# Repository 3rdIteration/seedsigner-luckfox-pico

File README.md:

# seedsigner-luckfox-pico
Port of the SeedSigner code to support the LuckFox Pico Linux board family. Since this device is still an embedded Linux device, like the Raspberry Pi, the changes are fairly minimal in order to access the buttons and the camera. This repo mostly pertains to the Buildroot OS build instructions, the KiCAD schematic and PCB design files, and 3D models of cases for the assembled device.

SeedSigner code fork: https://github.com/3rdIteration/seedsigner/tree/dev

## Hardware Photos
_Most Recent Iteration: LuckFox Pico Mini B with no onboard SPI flash_

_Previous Iteration: LuckFox Pico Pro Max (More Flash, SPI Flash)_

## Demo Videos

### First Look: SeedSigner running on LuckFox Pico Linux devboard

## Materials Needed
Check out the shopping list for a parts list of various LuckFox-based hardware configurations: [here](docs/shopping_list.md)

These example builds can build a device for around $60.

## OS Image Build with Buildroot

### Build with GitHub Actions (Recommended for Most Users)
The easiest way to build the SeedSigner OS image is using GitHub Actions. This method builds directly on GitHub's infrastructure without requiring Docker:

1. Fork this repository to your GitHub account
2. Navigate to the "Actions" tab in your fork
3. Select the "Build SeedSigner OS" workflow
4. The workflow runs automatically on pushes to `main`, `develop`, or `master` branches
5. Builds are created for both LuckFox Pico Mini (RV1103) and Pro Max (RV1106) hardware
6. Wait for the build to complete (typically 60-120 minutes)
7. Download the artifacts from the workflow run

The GitHub Actions workflow:
- Installs all required dependencies on Ubuntu 22.04
- Clones the LuckFox Pico SDK (customized fork), SeedSigner code, and SeedSigner OS packages
- Configures buildroot with SeedSigner-specific packages
- Builds the complete OS image
- Creates flashable SD card images and NAND flash bundles for SD_CARD and SPI_NAND boot media
- Provides detailed build summaries and flashing instructions

### Build Locally with Docker (Simple Method)
For users who want to build locally, a simple build script is available:

```bash
cd buildroot/
./build.sh build --microsd
```

Build artifacts will be automatically available in `buildroot/build-output/`. The script handles Docker image building, repository caching, and artifact export automatically.

**Additional options:**
- `--nand` - Build NAND flash bundles
- `--model mini` or `--model max` - Build specific hardware only
- `--jobs N` - Use N parallel jobs
- See `./build.sh --help` for all options

### Build Locally Without Docker (Advanced Users)
For development or if you prefer not to use Docker, an automated local build script is available (Ubuntu 22.04):

```bash
cd buildroot/
./build-local.sh --check-deps  # Install dependencies (first time)
./build-local.sh               # Build for Mini with SD card
```

**Additional options:**
- `--hardware mini|max` - Choose hardware type
- `--boot sd|nand` - Choose boot medium
- See `./build-local.sh --help` for all options

For more details and manual step-by-step instructions, see [OS-build-instructions.md](docs/OS-build-instructions.md).
For Luckfox runtime startup order, camera service sequencing, and Mini memory/timing behavior, see [LUCKFOX_STARTUP_WORKFLOW.md](docs/LUCKFOX_STARTUP_WORKFLOW.md).

## Dev Machine Setup

### Install ADB
Developing for the LuckFox Pico device is quite convenient since the devices never connect to the internet and you can access the device shell using `adb`. You can push files back and forth to your dev machine, and you can access the device as a shell easily.
```
# mac
brew install homebrew/cask/android-platform-tools

# linux
sudo apt install android-tools-adb
```

### ADB Connection and Device Management

1. Connect to the device:
```
# List connected devices
adb devices

# Connect to device shell
adb shell
```

2. File Operations:
```
# Push files to device
adb push local_file.txt /remote/path/

# Sync the code repo for local development
adb push /repos/seedsigner/src /seedsigner

# Pull files from device
adb pull /seedsigner/config.json .

# List files on device
adb shell ls /path/to/directory
```

## Hardware Identification
Notice the left device has an empty PCB footprint pattern on it. This is where the optional SPI flash is soldered on. For the SeedSigner project we don't want permanent storage, so avoid devices with soldered SPI flash.

```
LEFT:  LuckFox Pico Mini A -> No Flash
RIGHT: LuckFox Pico Mini B -> Soldered Flash
```

## Flashing the Device

### Flash MicroSD Card
```
sudo dd bs=4M status=progress if=seedsigner-luckfox-pico-YYYYmmdd_hhmmss.img of=/dev/diskX
```
Replace `/dev/diskX` with your actual SD card device path.

## LuckFox Pico OS Modifications
We have forked the [LuckFox Pico SDK](https://github.com/3rdIteration/luckfox-pico) in order to enable various hardware features like pull-up resistors, adjust video RAM, and other things.

### Camera Memory
The LuckFox devotes some of its memory for camera-related algorithms, but we don't use this feature. Particularly on the LuckFox Pico Mini device, which only has 64MB of RAM, it is beneficial for us to reclaim a bit of this memory.

**Note:** The GitHub Actions workflow automatically sets the CMA (Contiguous Memory Allocator) size to 1M for Mini builds, freeing up approximately 20MB of RAM. This is configured by modifying `RK_BOOTARGS_CMA_SIZE` in the board configuration file.

Memory usage WITHOUT modification:
```bash
[root@luckfox ]# free -h
              total        used        free      shared  buff/cache   available
Mem:          33.0M       24.3M        1.4M      476.0K        7.3M        5.4M
Swap:             0           0           0
```

Memory usage WITH modification:
```bash
[root@luckfox ]# free -h
              total        used        free      shared  buff/cache   available
Mem:          53.0M       23.6M        1.9M      472.0K       27.5M       25.3M
Swap:             0           0           0
```

### Pull-up Resistors
Our current dev board has external pull-up resistors, since we didn't know how to enable these at the time, and it is always smart to plan ahead when designing PCBs. NOTE: Even with this commit and this change, the internal pull-ups don't seem to work.

### SPI Buffer Size
While it is possible to send SPI data in chunks, you can increase the SPI buffer size to slightly increase throughput, which is useful for larger displays.

### PWM Output
In order to control the LCD screen backlight and support true dimming of the display (instead of just changing the background color of the QR code, for example), we had to enable a PWM on a specific output pin.

## Support the Developer
If you find this project helpful and would like to support its development, you can buy me a coffee! Your support helps keep this project going and funds future improvements. Help decentralize Bitcoin hardware!

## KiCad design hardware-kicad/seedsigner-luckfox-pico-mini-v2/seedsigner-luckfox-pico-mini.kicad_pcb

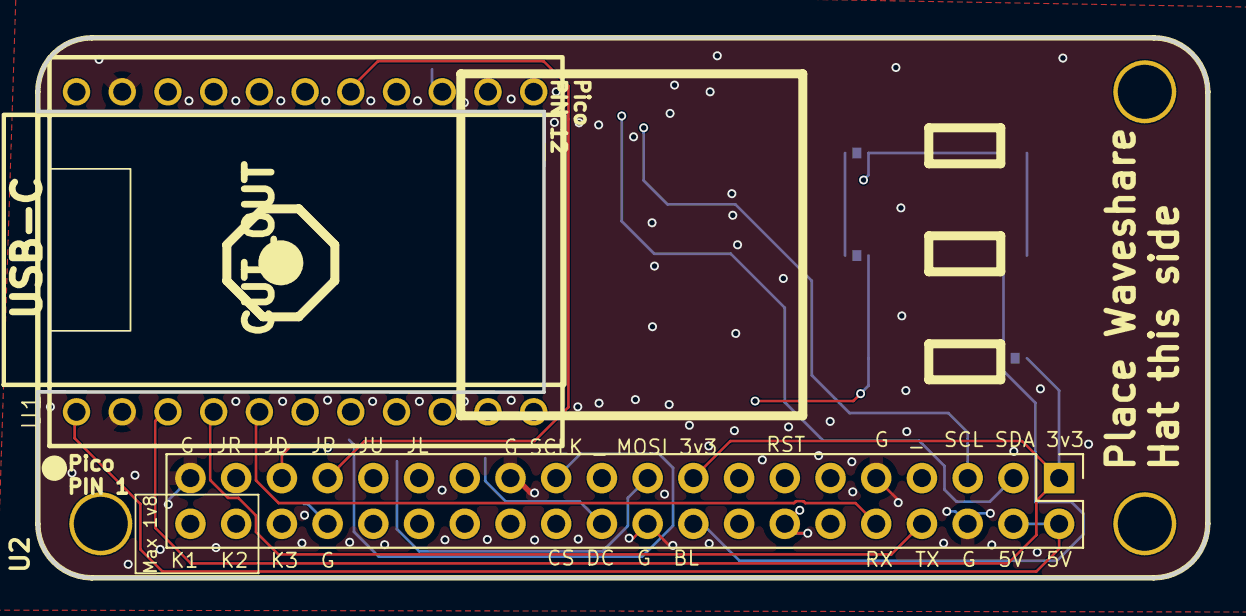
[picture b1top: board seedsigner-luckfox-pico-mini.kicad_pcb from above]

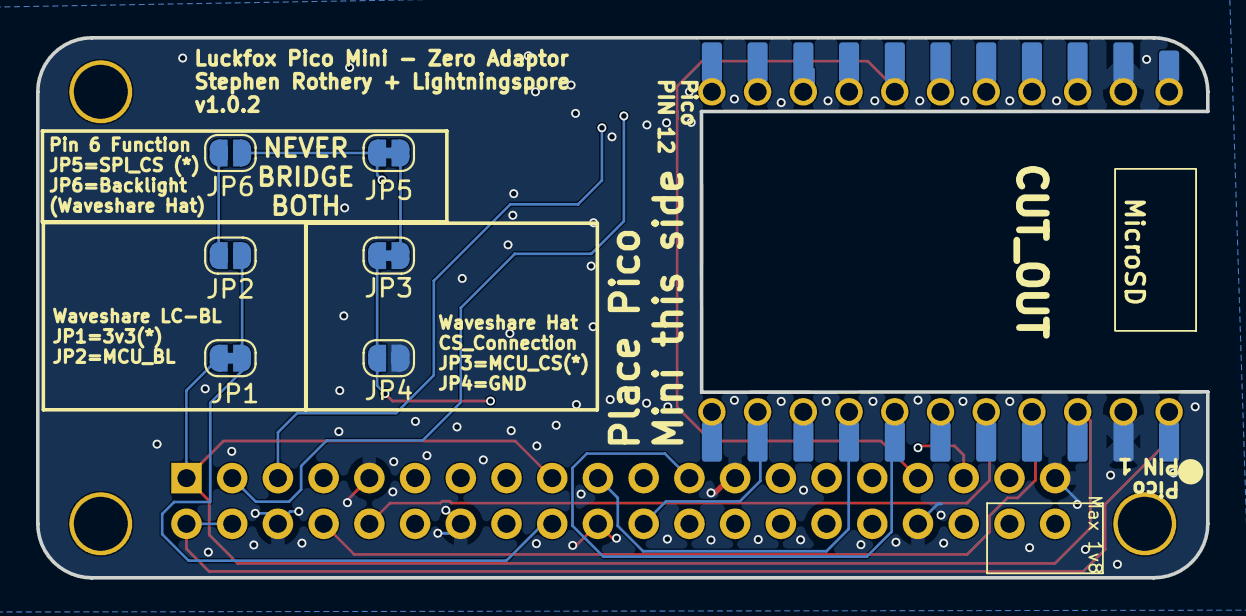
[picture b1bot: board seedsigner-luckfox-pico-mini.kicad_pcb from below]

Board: 4 copper layers, 65.0 x 30.0 mm, 8 parts (6 on the bottom side), 24 nets.

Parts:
JP1, JP3, JP5: Jumper_2_Small_Bridged; SolderJumper-2_P1.3mm_Bridged_RoundedPad1.0x1.5mm
JP2, JP4, JP6: Jumper_2_Small_Open; SolderJumper-2_P1.3mm_Open_RoundedPad1.0x1.5mm
U1: LuckFox_Pico_MINI; LUCKFOX_PICO_MINI
U2: WAVESHARELCD_PLUS_UART_PLUS_I2C; WAVESHARE_LCD_BUTTON

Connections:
+3.3V: JP1.1 (A), U1.3 (3V3(OUT)), U2.1 (3V3), U2.17 (3V3)
+5V: U1.1 (VBUS), U2.2 (5V0), U2.4 (5V0)
/DC: U1.10 (GPIO1_C4_d), U2.22 (DC)
/I2C-SCL: U1.15 (GPIO1_D3_d), U2.5 (I2C-SCL)
/I2C-SDA: U1.14 (GPIO1_D2_d), U2.3 (I2C-SDA)
/JOYSTICK_DOWN: U1.17 (GPIO1_C7_d), U2.35 (JS_DOWN)
/JOYSTICK_LEFT: U1.12 (GPIO1_D0_d), U2.29 (JS_LEFT)
/JOYSTICK_PRESS: U1.16 (GPIO1_C6_d), U2.33 (JS_PRESS)
/JOYSTICK_RIGHT: U1.18 (GPIO0_A4_d), U2.37 (JS_RIGHT)
/JOYSTICK_UP: U1.13 (GPIO1_D1_d), U2.31 (JS_UP)
/KEY1: U1.19 (GPIO4_C0_z), U2.40 (KEY1)
/KEY2: U1.20 (GPIO4_C1_z), U2.38 (KEY2)
/KEY3: U1.11 (GPIO1_C5_d), U2.36 (KEY3)
/MCU_BACKLIGHT: JP2.1 (A), JP6.1 (A)
/MCU_SPI_CS: JP3.1 (A), JP5.1 (A)
/RPI_BACKLIGHT: JP1.2 (B), JP2.2 (B), U2.18 (BACKLIGHT)
/RPI_SPI_CS: JP3.2 (B), JP4.2 (B), U2.24 (~SPI_CS0)
/RST: U1.9 (SPI0_MISO_M0/GPIO1_C3_d), U2.13 (RESET)
/SPI_MOSI: U1.8 (SPI0_MOSI_M0/GPIO1_C2_d), U2.19 (SPI_MOSI)
/SPI_SCLK: U1.7 (SPI0_CLK_M0/IO1_C1_d), U2.23 (SPI_SCLK)
/UART_RXD: U1.5 (GPIO1_B3_u), U2.10 (UART-RXDO)
/UART_TXD: U1.4 (GPIO1_B2_d), U2.8 (UART-TXDO)
GND: JP4.1 (A), U1.2 (GND), U1.21 (GND), U2.6 (GND), U2.9 (GND), U2.14 (GND), U2.20 (GND), U2.25 (GND), U2.30 (GND), U2.34 (GND), U2.39 (GND)
unnamed: JP5.2 (B), JP6.2 (B), U1.6 (SPI0_CS0_M0/IO1_C0_d)

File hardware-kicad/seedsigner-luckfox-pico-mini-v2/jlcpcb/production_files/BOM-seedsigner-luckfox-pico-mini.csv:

Comment,Designator,Footprint,LCSC,Quantity
LuckFox_Pico_MINI,U1,LUCKFOX_PICO_MINI,,1
WAVESHARELCD_PLUS_UART_PLUS_I2C,U2,WAVESHARE_LCD_BUTTON,,1
Jumper_2_Small_Open,JP2,SolderJumper-2_P1.3mm_Open_RoundedPad1.0x1.5mm,,1
Jumper_2_Small_Open,JP4,SolderJumper-2_P1.3mm_Open_RoundedPad1.0x1.5mm,,1
Jumper_2_Small_Open,JP6,SolderJumper-2_P1.3mm_Open_RoundedPad1.0x1.5mm,,1
Jumper_2_Small_Bridged,JP3,SolderJumper-2_P1.3mm_Bridged_RoundedPad1.0x1.5mm,,1
Jumper_2_Small_Bridged,JP1,SolderJumper-2_P1.3mm_Bridged_RoundedPad1.0x1.5mm,,1
Jumper_2_Small_Bridged,JP5,SolderJumper-2_P1.3mm_Bridged_RoundedPad1.0x1.5mm,,1

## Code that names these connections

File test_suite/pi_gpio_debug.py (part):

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    KEY_RIGHT = GPIO0_A0  gpiochip0/0
    KEY_DOWN  = GPIO0_A1  gpiochip0/1
    KEY_PRESS = GPIO1_C4  gpiochip1/20
    KEY3      = GPIO1_C7  gpiochip1/23
    KEY_UP    = GPIO3_D1  gpiochip3/25
    KEY_LEFT  = GPIO3_D2  gpiochip3/26
    KEY2      = GPIO3_D3  gpiochip3/27
    KEY1      = GPIO4_C1  gpiochip4/17

Register addresses from docs/RV1106_GPIO_User_Manual.txt
(extracted from Rockchip_RV1106_User_Manual_GPIO.pdf).
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    ("KEY_UP",    3, 25,   0xFF558058,  6, 4,  0xFF5581AC,  1,  0xFF5581EC,  3, 2, 'std',   0xFF55000C,  9,  0xFF550074,  9),
    ("KEY_LEFT",  3, 26,   0xFF558058, 10, 8,  0xFF5581AC,  2,  0xFF5581EC,  5, 4, 'std',   0xFF55000C, 10,  0xFF550074, 10),
    ("KEY2",      3, 27,   0xFF558058, 14,12,  0xFF5581AC,  3,  0xFF5581EC,  7, 6, 'std',   0xFF55000C, 11,  0xFF550074, 11),
    ("KEY1",      4, 17,   0xFF568010,  6, 4,  0xFF5680C0,  3,  0xFF5680C0, 14,13, 'gpio4hd', 0xFF56000C, 1, 0xFF560074,  1),
]


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        (0xFF388030, 0x00030003, 'GPIO0 input buffer enable'),
        (0xFF388038, 0x000F0005, 'GPIO0 pull-up'),
        (0xFF380008, 0x00030000, 'GPIO0 direction → input'),
        # GPIO1: KEY_PRESS (C4) + KEY3 (C7)
        (0xFF538014, 0x70070000, 'GPIO1 IOMUX → GPIO'),
        (0xFF538188, 0x00900090, 'GPIO1 input buffer enable'),
        (0xFF5381C8, 0xC3004100, 'GPIO1 pull-up'),
        (0xFF53000C, 0x00900000, 'GPIO1 direction → input'),
        # GPIO3: KEY_UP (D1) + KEY_LEFT (D2) + KEY2 (D3)
        (0xFF558058, 0x77700000, 'GPIO3 IOMUX → GPIO'),
        (0xFF5581AC, 0x000E000E, 'GPIO3 input buffer enable'),
        (0xFF5581EC, 0x00FC0054, 'GPIO3 pull-up'),
        (0xFF55000C, 0x0E000000, 'GPIO3 direction → input'),
        # GPIO4: KEY1 (C1) — high-drive pad, pull encoding: 3=pullup
        (0xFF568010, 0x00700000, 'GPIO4 IOMUX → GPIO'),
        (0xFF5680C0, 0x60086008, 'GPIO4 pull-up + input buffer enable'),
        (0xFF56000C, 0x00020000, 'GPIO4 direction → input'),
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    print('    gpioget -c gpiochip0 0   # KEY_RIGHT')
    print('    gpioget -c gpiochip0 1   # KEY_DOWN')
    print('    gpioget -c gpiochip1 20  # KEY_PRESS')
    print('    gpioget -c gpiochip1 23  # KEY3')
    print('    gpioget -c gpiochip3 25  # KEY_UP')
    print('    gpioget -c gpiochip3 26  # KEY_LEFT')
    print('    gpioget -c gpiochip3 27  # KEY2')
    print('    gpioget -c gpiochip4 17  # KEY1')
    print()
    print('  Force IOMUX → GPIO for all button pins via kernel pinctrl:')
    print('    gpioget -c gpiochip0 0 1')
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
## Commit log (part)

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2026-02-11 Fix cryptography cargo target injection order for armv7
2026-02-11 Use GCC 11 buildroot toolchain for libcamera compatibility
2026-02-12 Add workflow_dispatch toggles for build and hardware targets
2026-02-12 Align GitHub build workflow with local build.sh invocation
2026-02-12 Make CI builds deterministic with optional upstream ref pinning
2026-02-13 CI: checkout workflow repo with recursive submodules
2026-02-13 Use recursive checkout for CI Docker and local jobs
2026-02-13 Pin SDK to external Buildroot defconfig
2026-02-13 Add CI rootfs UBI sanity checks and debug logging
2026-02-13 Add local build diagnostics and rootfs sanity checks
2026-02-13 Build: run rootfs UBI sanity checks only for NAND outputs
2026-02-13 CI: split mini/max x sd/nand builds and collect NAND debug artifacts
2026-02-13 Fix workflow concurrency expression to avoid matrix context error
2026-02-13 Fix matrix medium filter expression in workflow
2026-02-13 Polish NAND sanity command formatting
2026-02-13 Force required Buildroot packages and rootfs overlay
2026-02-13 Fix BR2_DEFCONFIG rewrite quoting after script refactor
2026-02-13 Fix SIGPIPE 141 in Buildroot dir discovery
2026-02-13 Require dynamic eudev device management in Buildroot config checks
2026-02-13 Fix export_variant_images to copy files directly to OUTPUT_DIR
    The export_variant_images function was creating a subdirectory
    ${board_profile}-${boot_medium}-images inside OUTPUT_DIR, causing
    GitHub Actions to fail finding rootfs.img. Changed to copy files
    directly to OUTPUT_DIR to match workflow expectations.
2026-02-13 Address code review feedback: combine sed calls and simplify logic
    - Combined multiple sed invocations into single command for better performance
    - Simplified eudev configuration logic to unconditionally ensure BR2_PACKAGE_EUDEV is set
    - Removed confusing conditional that was always setting the same value
2026-02-13 Fix buildroot config fragment to disable conflicting device creation methods
2026-02-14 Add explicit permissions to workflow jobs for security
    - Add permissions block to setup job (contents: read)
    - Add permissions block to build job (contents: read, actions: write)
    - Fixes CodeQL security alerts about missing workflow permissions
2026-02-14 Fix shell script issues in workflow for better handling of filenames with spaces
2026-02-14 Fix artifact duplication - filter by model in uploads
    - Modified "Package NAND bundle zips" to only process current model's bundles
    - Updated artifact upload paths to be model-specific using matrix.model
    - Updated "List build artifacts" to show only current model's files
    - Updated "Build summary" to filter artifacts by model
    - This ensures each job only uploads artifacts for its specific model/medium combination
2026-02-14 Remove tar.gz NAND bundles - only keep zip format
    - Removed tar.gz creation from os-build.sh create_nand_image_artifacts
    - Removed export_official_nand_image_dir function (only created tar.gz)
    - Removed tar.gz from workflow artifact upload paths
    - Removed tar.gz listing and summary sections from workflow
    - Updated documentation to reflect single zip format
    - NAND bundles now only created as .zip for cross-platform compatibility
2026-02-14 Improve code maintainability: add SYSTEM_INDEX variable and share board config path
2026-02-14 Add repository URL inputs to GitHub Actions workflow for flexibility
2026-02-14 Fix pyzbar library path by symlinking zbar.so from site-packages to /usr/lib
2026-02-14 Fix documentation inconsistencies based on code review
2026-02-14 Fix dependency detection in build-local.sh using dpkg-query
2026-02-14 Add comprehensive documentation for libcamera build fix
2026-02-15 Update SDK to 3rdIteration/luckfox-pico with GCC 13 support
    This fixes the build failure caused by libcamera requiring GCC 9.0+
    The previous SDK (lightningspore/luckfox-pico) used an older GCC version
    Changes:
    - Update GitHub Actions workflow to use 3rdIteration/luckfox-pico@copilot/enable-glibc-highest-version
    - Update all build scripts to use the new SDK repository and branch
    - Update documentation to reflect the new SDK location
2026-02-15 Switch local and CI builds to glibc LuckFox SDK
2026-02-15 Add SDK compiler alias fallback for buildroot_create
2026-02-15 Fix stub toolchain interfering with actual compilation
    The stub toolchain was being added to GITHUB_PATH, which persists
    across all workflow steps. This caused the stub to be used during
    actual compilation (u-boot build), which failed as designed.
    Changed to only export PATH within the "Prepare buildroot source tree"
    step, so the stub is only available for the Makefile.param check.
    Subsequent build steps (u-boot, kernel, rootfs) will use buildroot's
2026-02-15 Update documentation with build.sh validation fix
2026-02-15 Build buildroot with 'make buildroot' to create toolchain and runtime libs
    The previous approach of using './build.sh rootfs' failed because it
    expected runtime libraries at /tmp/runtime_lib, which are only created
    during the full buildroot build process.
    Changed to use 'make buildroot -C sysdrv' which:
    1. Builds buildroot's internal GCC 13 toolchain
    2. Creates runtime libraries in /tmp/runtime_lib
2026-02-15 Fix build failure by copying rootfs-overlay to expected location
2026-02-15 Upgrade to buildroot 2024.11.1 with Python 3.12
2026-02-15 Fix all placeholder hashes with correct SHA256 checksums
    - nfc-bindings: updated from placeholder to d5a562ee...
    - openct: updated from placeholder to f1ba0147...
    - python-pyscard: updated from placeholder (v2.1.1) to correct hash for v2.3.1
    All hashes verified by downloading actual release tarballs from GitHub.
2026-02-15 Fix build: remove python-cryptography and dependencies from buildroot
    Remove BR2_PACKAGE_PYTHON_CRYPTOGRAPHY, BR2_PACKAGE_PYTHON_PYASN1, and
    BR2_PACKAGE_PYTHON_PYOPENSSL from buildroot defconfig and python-pgpy
    dependencies.
    These packages will be installed by SeedSigner's pip installation instead.
    python-cryptography in buildroot 2024.11.x has Rust components that fail
    to cross-compile for ARM. seedsigner-os uses buildroot 2023.02.x which has
2026-02-16 Fix opencv-mobile package: correct version tag and Python paths
    - Use version 35 (tag v35) instead of 4.13.0
    - Update hash to match v35 tarball (4411be32...)
    - Fix Python CMake variables: PYTHON3_INCLUDE_PATH and PYTHON3_PACKAGES_PATH
    - Remove PYTHON3_NUMPY_INCLUDE_DIRS (automatically detected by OpenCV)
    - Fix HOST_DIR path from /bin to /usr/bin
    These fixes address code review feedback and ensure proper build configuration.
2026-02-16 Disable opencv-mobile due to numpy GCC requirement, revert to custom NV12 converter
    NumPy requires GCC >= 8.4 but LuckFox toolchain has older GCC version.
    opencv-mobile Python bindings require numpy, which cannot be built.
    Changes:
    - Disabled BR2_PACKAGE_OPENCV_MOBILE in defconfig
    - Disabled BR2_PACKAGE_OPENCV_MOBILE_PYTHON in defconfig
    - Reverted default branch to claude/add-luckfox-pico-support-AO5ZX
2026-02-16 Use buildroot's bundled numpy and new LuckFox SDK branch with higher uclibc
    Removed custom python-numpy package and switched to using buildroot's bundled
    numpy. The new LuckFox SDK branch (copilot/build-python-with-uclib-nh) has a
    higher version of uclibc that should support the GCC requirements for numpy.
    Changes:
    - Removed buildroot/external-packages/python-numpy/ directory entirely
    - Removed python-numpy from Computer Vision menu in workflow
2026-02-16 Fix legacy configuration error: Create minimal clean defconfig
    The build was failing with "legacy configuration" error because the defconfig
    had 517 lines of auto-generated computed values (BR2_TOOLCHAIN_HEADERS_AT_LEAST_*,
    BR2_PACKAGE_*_ARCH_SUPPORTS, etc.) that shouldn't be in a defconfig file.
    Created a minimal defconfig (~140 lines) with only the explicitly user-selected
    options:
    - Architecture: ARM Cortex-A7, hard float, VFPv4
2026-02-16 Fix legacy configuration: Remove BR2_PACKAGE_OVERRIDE_FILE and empty post-script options
    Removed legacy/problematic configuration options that were causing the
    "legacy configuration" error:
    - BR2_PACKAGE_OVERRIDE_FILE (not standard, using invalid path)
    - BR2_ROOTFS_POST_IMAGE_SCRIPT="" (empty value, not needed)
    - BR2_ROOTFS_POST_SCRIPT_ARGS="" (empty value, not needed)
    These options were likely triggering buildroot's legacy configuration check.
2026-02-17 Enable rng-tools for hardware random number generation
2026-02-17 Enable libgpiod2 library and tools for GPIO control
2026-02-17 Complete SPI-NAND investigation: partition layout and space analysis
2026-02-17 Add implementation summary for automated patch system
2026-02-17 Add documentation for GitHub Actions workflow triggers
2026-02-17 Add python-pyscard and python-pysatochip smartcard support packages
2026-02-17 Fix python-pyscard build failure by adding pcsc-lite dependency
2026-02-17 Fix userdata removal from partition filesystem configuration
2026-02-19 Add comprehensive planning document for camera service management
2026-02-19 Expand Pro Max rootfs to 227MB for 256MB flash
2026-02-19 Fix rkipc patch timing and stabilize camera init startup
2026-02-20 Increase delayed rkaiq service start by 5 seconds
2026-02-20 Update start-seedsigner.sh
    Give camera server a bit longer delay (needed on mini on microsd)
2026-02-21 feat: add Luckfox Pico Pi support (eMMC build)
    - os-build.sh: add 'pi' profile (hw_index=7), 'emmc' boot medium, create_emmc_bundle(), run_automated_build pi support
    - build-local.sh: add 'pi' hardware, 'emmc' boot, create_emmc_bundle(), update CLI validation
    - build.yml: add RV1106_Luckfox_Pico_Pi hw option, EMMC boot option, pi/EMMC matrix entry, Configure board for pi/EMMC, Create eMMC flash bundle step, eMMC build summary
2026-02-21 build: remove Pi eMMC userdata partition in all build paths
2026-02-21 build: patch DTS bootargs to disable UART2 console and fail CI if boot.img still has it
2026-02-21 Disable kernel FIQ debugger when UART2 debug is disabled
2026-02-21 build: disable UART2 console by default and default python fallback t… (#32)
    * build: disable UART2 console by default and default python fallback to 3.12
    * build: apply UART2 console cleanup to active .BoardConfig.mk
    * build: avoid editing .BoardConfig.mk symlink for UART2 console patch
    * ci: add .zip extension to uploaded artifact names
    * build: add UART bootargs debug logging across all build paths
    * build: patch DTS bootargs to disable UART2 console and fail CI if boot.img still has it
2026-02-22 Add persistent pcscd init supervisor and debugging tools
2026-02-22 Enable embedded mode for ccid-sec1210 package
2026-02-22 Fix luckfox MISO enable mapping for Pi vs Mini/Max (#34)
2026-02-23 ci: fail fast on invalid hardware/boot combinations
2026-03-01 Fix outdated comments about RkLunch.sh camera behavior
2026-03-03 Fix Pi ghost inputs: reset I2C3/PWM1 via /dev/mem in start-seedsigner.sh
2026-03-03 Extend Pi GPIO pull-up fix to all 8 buttons; add RV1106 GPIO manual; document python-periphery limitation
2026-03-04 Add Rockchip RV1106 GPIO manual PDF to docs/
2026-03-04 Enable HWRNG and hardware crypto in kernel defconfig and DTS across all build profiles
2026-03-05 docs: document /dev/gpiochip4 missing on Pico Mini in LUCKFOX_STARTUP_WORKFLOW.md
2026-03-05 Add FAT fsck support to S02fsck: repair stuck-ro FAT partitions at boot
2026-03-05 docs: update LUCKFOX_STARTUP_WORKFLOW to reflect unconditional Mini gpiochip4 symlink
2026-03-08 Fix python-pgpy build: remove python-cryptography dep (incompatible with uclibc)
2026-03-09 Enable Rust from source and python-cryptography for uclibc target
    - Add BR2_PACKAGE_PYTHON_CRYPTOGRAPHY=y to defconfig
    - Switch from host-rust-bin to host-rust (build from source) since
    pre-built rust-std binaries don't exist for uclibc Tier 3 targets
    - Add BR2_PACKAGE_HOST_RUSTC_TARGET_TIER3_UCLIBC_PLATFORMS=y
    - Add BR2_PACKAGE_HOST_RUSTC_TARGET_ARCH_SUPPORTS=y
    - Add RUST_UCLIBC_SUPPORT.md documenting the required SDK patches
2026-03-09 Enable gnupg2 with pinentry, optimize Mini image by removing pip/setuptools/git
2026-03-09 Fix code review issues: find precedence, remove broken dl path, update Dockerfile
    - Fix find -type f -o -type l precedence with parentheses
    - Remove broken ../dl path reference from workflow
    - Add cache/ COPY to Dockerfile for Docker builds
2026-03-09 Host Rust toolchain cache as GitHub Release asset
    Replace Git LFS / split chunks with a GitHub Release approach:
    - CI downloads toolchain from releases/download/rust-toolchain/
    - After building from source, CI auto-uploads to the release
    - No large files in git history, no LFS needed
    - Supports RUST_TOOLCHAIN_REPO_URL override for forks
    - All 3 build scripts (build.yml, os-build.sh, build-local.sh) updated
